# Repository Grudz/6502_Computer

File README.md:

# 6502_Computer
This repository stores everything for my 6502 project. This includes schematics, datasheets, C scripts, and assembly programs
.
[Ben Eater](https://www.youtube.com/playlist?list=PLowKtXNTBypFbtuVMUVXNR0z1mu7dp7eH) designed a custom clock module and 6502 computer on a breadboard. I expanded on that project, by combining those and turning them into a PCB.

-----
### Pretty dope red PCB I designed (4 layers:wink:)

### My Breadboard, not too shabby:sunglasses:

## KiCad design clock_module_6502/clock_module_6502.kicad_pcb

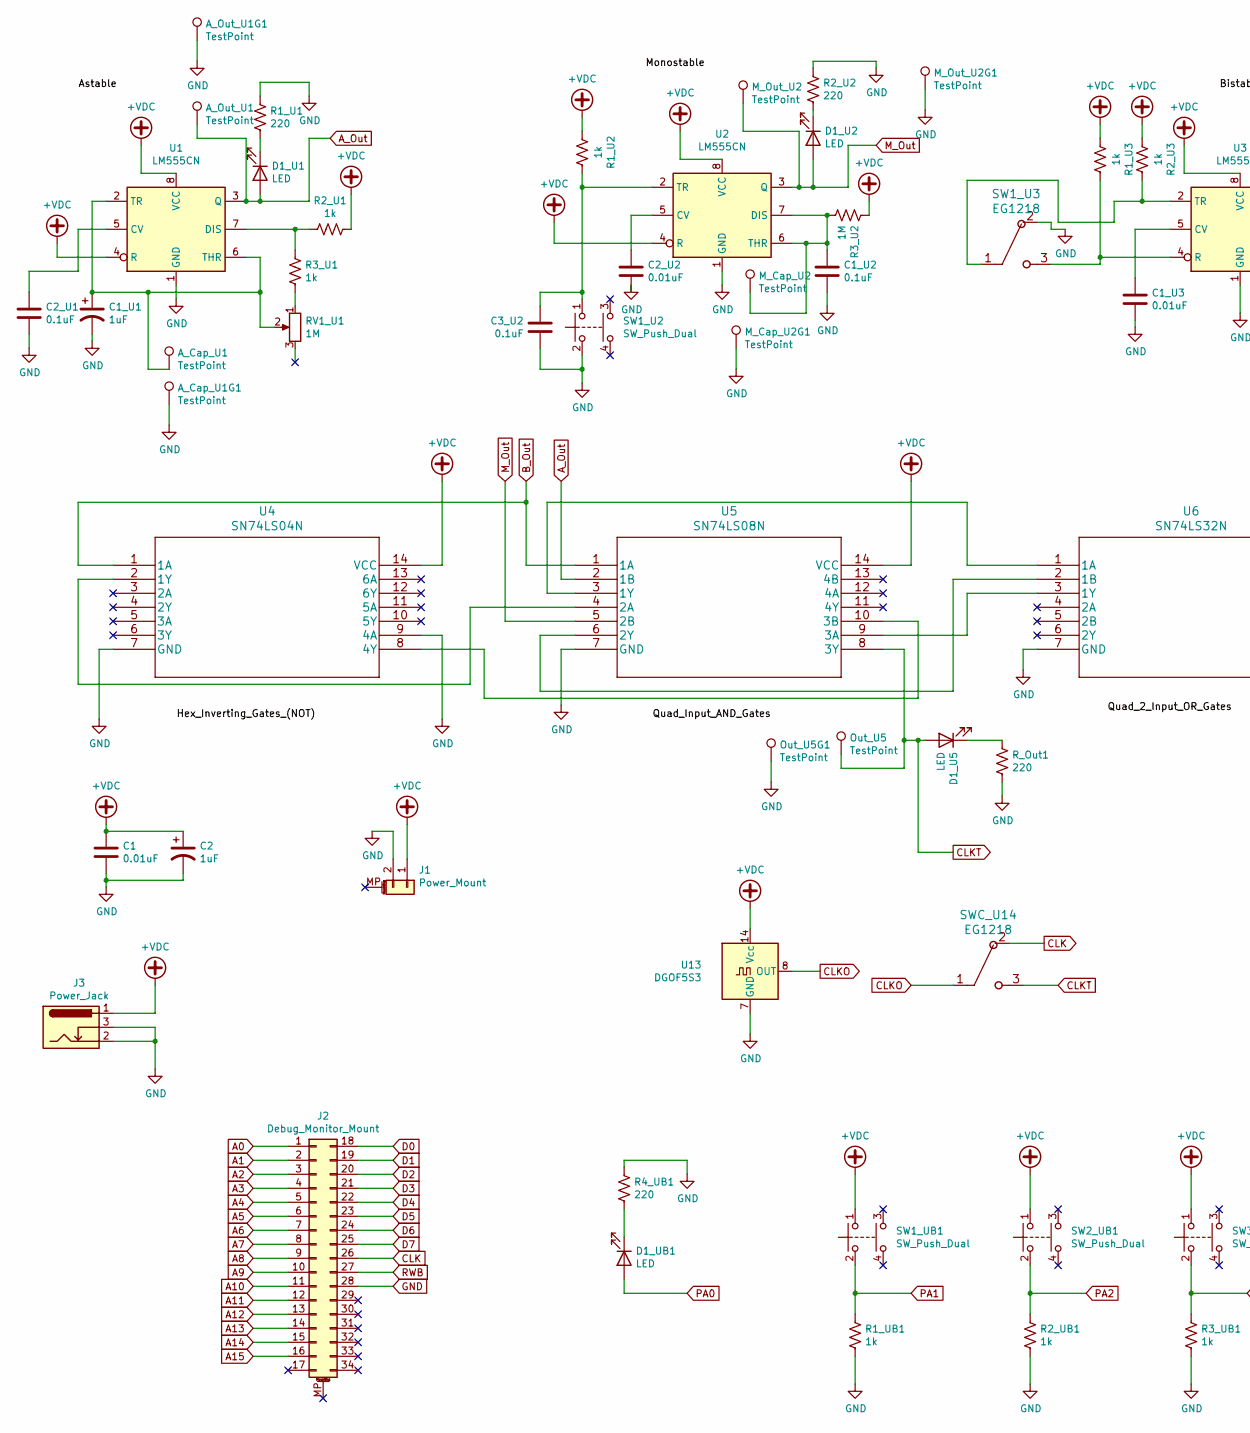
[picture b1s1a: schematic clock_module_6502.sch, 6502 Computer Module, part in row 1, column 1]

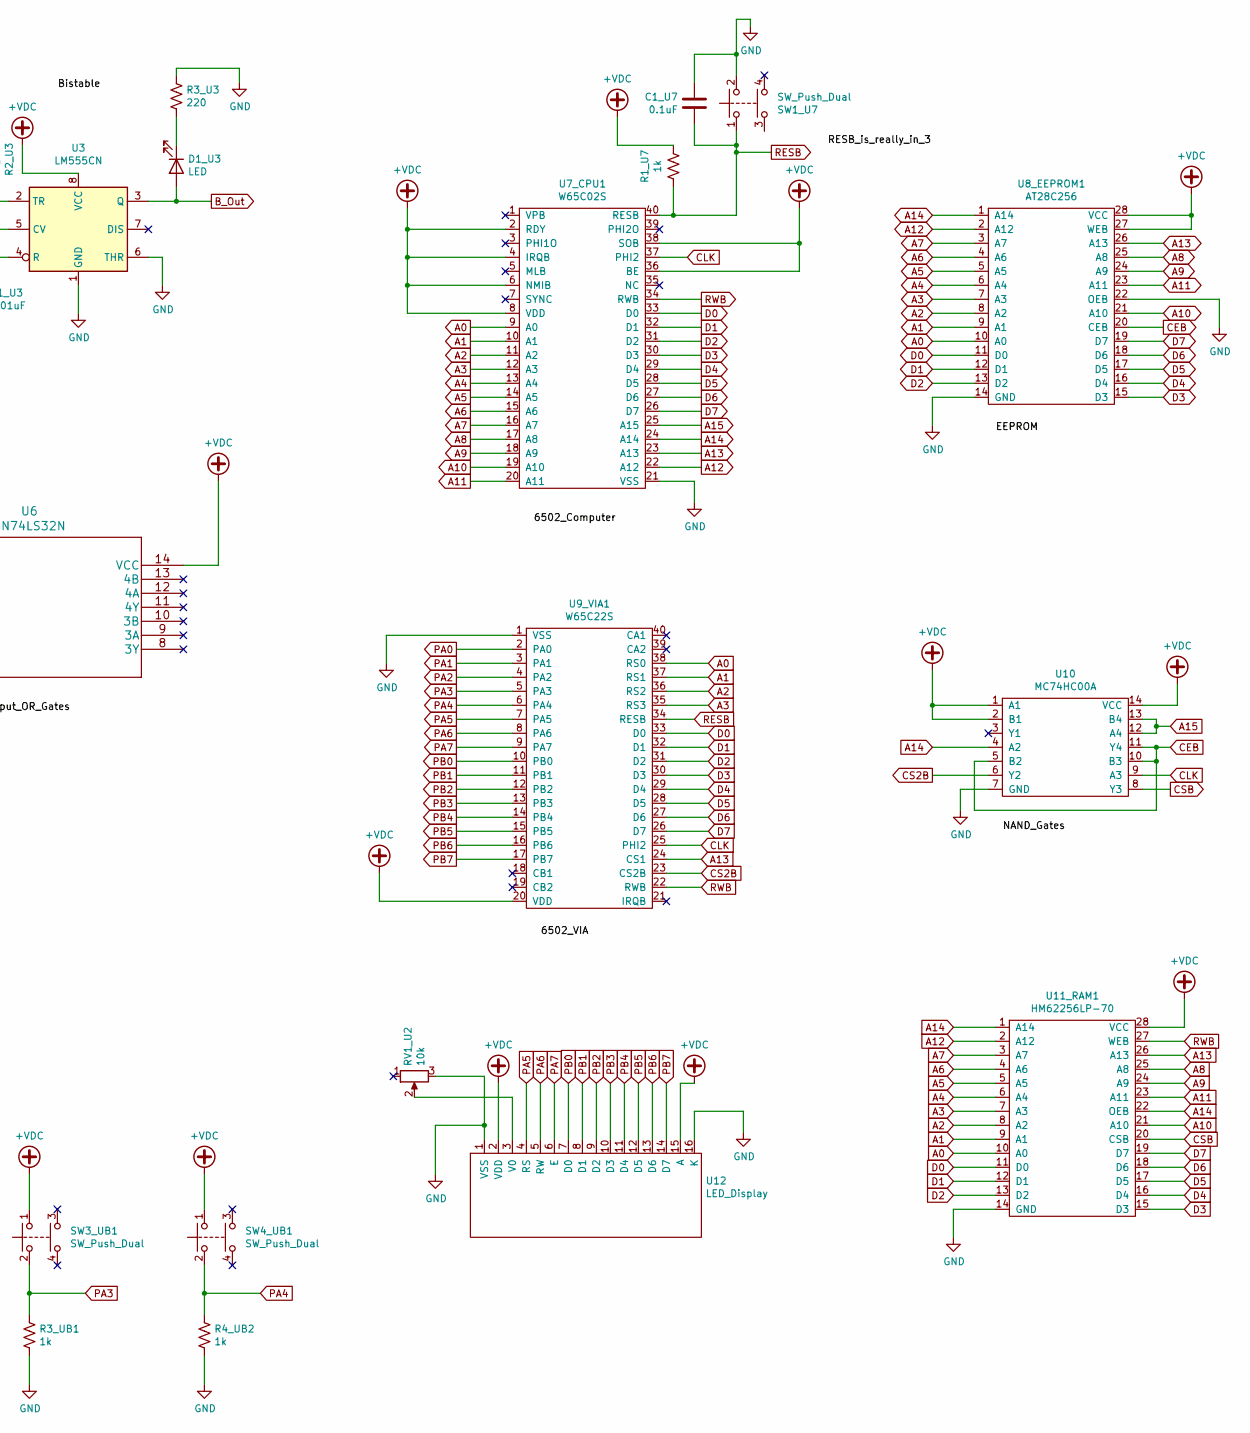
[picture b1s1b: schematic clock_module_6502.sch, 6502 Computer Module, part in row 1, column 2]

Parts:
A_Cap_U1, A_Cap_U1G1: TestPoint; TestPoint_Keystone_5000-5004_Miniature
A_Out_U1, A_Out_U1G1: TestPoint; TestPoint_Keystone_5000-5004_Miniature
C1, C1_U3, C2_U2: 0.01uF; C_Disc_D7.5mm_W5.0mm_P5.00mm
C1_U1, C2: 1uF; CP_Radial_D5.0mm_P2.50mm
C1_U2, C1_U7, C2_U1, C3_U2: 0.1uF; C_Disc_D7.5mm_W5.0mm_P5.00mm
D1_U1, D1_U2, D1_U3, D1_U5, D1_UB1: LED; LED_D3.0mm_FlatTop
J1: Power_Mount; PinHeader_1x02_P2.54mm_Vertical
J2: Debug_Monitor_Mount; PinHeader_2x17_P2.54mm_Vertical
J3: Power_Jack; BarrelJack_Horizontal
M_Cap_U2, M_Cap_U2G1: TestPoint; TestPoint_Keystone_5000-5004_Miniature
M_Out_U2, M_Out_U2G1: TestPoint; TestPoint_Keystone_5000-5004_Miniature
Out_U5, Out_U5G1: TestPoint; TestPoint_Keystone_5000-5004_Miniature
R1_U1, R2_U2, R3_U3, R4_UB1: 220; R_1206_3216Metric_Pad1.42x1.75mm_HandSolder
R1_U2, R1_U3, R1_U7, R1_UB1, R2_U1, R2_U3, R2_UB1, R3_U1, R3_UB1, R4_UB2: 1k; R_1206_3216Metric_Pad1.42x1.75mm_HandSolder
R3_U2: 1M; R_1206_3216Metric_Pad1.42x1.75mm_HandSolder
RV1_U1: 1M; Potentiometer_Bourns_3296W_Vertical
RV1_U2: 10k; Potentiometer_Bourns_3296W_Vertical
R_Out1: 220; R_1206_3216Metric_Pad1.42x1.75mm_HandSolder
SW1_U2, SW1_U7, SW1_UB1, SW2_UB1, SW3_UB1, SW4_UB1: SW_Push_Dual; SW_Tactile_Straight_KSL0Axx1LFTR
SW1_U3: EG1218
SWC_U14: EG1218
U1, U2, U3: LM555CN; DIP-8_W7.62mm
U4: SN74LS04N; SN74LS32N
U5: SN74LS08N; SN74LS32N
U6: SN74LS32N
U7_CPU1: W65C02S; DIP-40_W15.24mm_Socket
U8_EEPROM1: AT28C256; DIP-28_W15.24mm_Socket
U9_VIA1: W65C22S; DIP-40_W15.24mm_Socket
U10: MC74HC00A; SN74LS32N
U11_RAM1: HM62256LP-70; DIP-28_W15.24mm_Socket
U12: LED_Display; WC1602A
U13: DGOF5S3; Oscillator_DIP-14

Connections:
+VDC: C1.1, C2.1, J1.1, J3.1, R1_U2.2, R1_U3.2, R1_U7.1, R2_U1.1, R2_U3.2, R3_U2.2, SW1_UB1.1, SW2_UB1.1, SW3_UB1.1, SW4_UB1.1, U1.4 (R), U1.8 (VCC), U2.4 (R), U2.8 (VCC), U3.8 (VCC), U4.14 (VCC), U5.14 (VCC), U6.14 (VCC), U7_CPU1.2 (RDY), U7_CPU1.4 (IRQB), U7_CPU1.6 (NMIB), U7_CPU1.8 (VDD), U7_CPU1.36 (BE), U7_CPU1.38 (SOB), U8_EEPROM1.27 (WEB), U8_EEPROM1.28 (VCC), U9_VIA1.20 (VDD), U10.1 (A1), U10.2 (B1), U10.14 (VCC), U11_RAM1.28 (VCC), U12.2 (VDD), U12.15 (A), U13.14 (Vcc)
A0: J2.1, U7_CPU1.9 (A0), U8_EEPROM1.10 (A0), U9_VIA1.38 (RS0), U11_RAM1.10 (A0)
A1: J2.2, U7_CPU1.10 (A1), U8_EEPROM1.9 (A1), U9_VIA1.37 (RS1), U11_RAM1.9 (A1)
A2: J2.3, U7_CPU1.11 (A2), U8_EEPROM1.8 (A2), U9_VIA1.36 (RS2), U11_RAM1.8 (A2)
A3: J2.4, U7_CPU1.12 (A3), U8_EEPROM1.7 (A3), U9_VIA1.35 (RS3), U11_RAM1.7 (A3)
A4: J2.5, U7_CPU1.13 (A4), U8_EEPROM1.6 (A4), U11_RAM1.6 (A4)
A5: J2.6, U7_CPU1.14 (A5), U8_EEPROM1.5 (A5), U11_RAM1.5 (A5)
A6: J2.7, U7_CPU1.15 (A6), U8_EEPROM1.4 (A6), U11_RAM1.4 (A6)
A7: J2.8, U7_CPU1.16 (A7), U8_EEPROM1.3 (A7), U11_RAM1.3 (A7)
A8: J2.9, U7_CPU1.17 (A8), U8_EEPROM1.25 (A8), U11_RAM1.25 (A8)
A9: J2.10, U7_CPU1.18 (A9), U8_EEPROM1.24 (A9), U11_RAM1.24 (A9)
A10: J2.11, U7_CPU1.19 (A10), U8_EEPROM1.21 (A10), U11_RAM1.21 (A10)
A11: J2.12, U7_CPU1.20 (A11), U8_EEPROM1.23 (A11), U11_RAM1.23 (A11)
A12: J2.13, U7_CPU1.22 (A12), U8_EEPROM1.2 (A12), U11_RAM1.2 (A12)
A13: J2.14, U7_CPU1.23 (A13), U8_EEPROM1.26 (A13), U9_VIA1.24 (CS1), U11_RAM1.26 (A13)
A14: J2.15, U7_CPU1.24 (A14), U8_EEPROM1.1 (A14), U10.4 (A2), U11_RAM1.1 (A14), U11_RAM1.22 (OEB)
A15: J2.16, U7_CPU1.25 (A15), U10.12 (A4), U10.13 (B4)
A_Out: A_Out_U1.1, D1_U1.2 (A), U1.3 (Q), U5.2 (1B)
B_Out: D1_U3.2 (A), U3.3 (Q), U4.1 (1A), U5.1 (1A)
CEB: U8_EEPROM1.20 (CEB), U10.5 (B2), U10.10 (B3), U10.11 (Y4)
CLK: J2.26, SWC_U14.2, U7_CPU1.37 (PHI2), U9_VIA1.25 (PHI2), U10.9 (A3)
CLKO: SWC_U14.1, U13.8 (OUT)
CLKT: D1_U5.2 (A), Out_U5.1, SWC_U14.3, U5.8 (3Y)
CS2B: U9_VIA1.23 (CS2B), U10.6 (Y2)
CSB: U10.8 (Y3), U11_RAM1.20 (CSB)
D0: J2.18, U7_CPU1.33 (D0), U8_EEPROM1.11 (D0), U9_VIA1.33 (D0), U11_RAM1.11 (D0)
D1: J2.19, U7_CPU1.32 (D1), U8_EEPROM1.12 (D1), U9_VIA1.32 (D1), U11_RAM1.12 (D1)
D2: J2.20, U7_CPU1.31 (D2), U8_EEPROM1.13 (D2), U9_VIA1.31 (D2), U11_RAM1.13 (D2)
D3: J2.21, U7_CPU1.30 (D3), U8_EEPROM1.15 (D3), U9_VIA1.30 (D3), U11_RAM1.15 (D3)
D4: J2.22, U7_CPU1.29 (D4), U8_EEPROM1.16 (D4), U9_VIA1.29 (D4), U11_RAM1.16 (D4)
D5: J2.23, U7_CPU1.28 (D5), U8_EEPROM1.17 (D5), U9_VIA1.28 (D5), U11_RAM1.17 (D5)
D6: J2.24, U7_CPU1.27 (D6), U8_EEPROM1.18 (D6), U9_VIA1.27 (D6), U11_RAM1.18 (D6)
D7: J2.25, U7_CPU1.26 (D7), U8_EEPROM1.19 (D7), U9_VIA1.26 (D7), U11_RAM1.19 (D7)
GND: A_Cap_U1G1.1, A_Out_U1G1.1, C1.2, C1_U1.2, C1_U2.2, C1_U3.2, C1_U7.1, C2.2, C2_U1.2, C2_U2.2, C3_U2.2, J1.2, J2.28, J3.2, J3.3, M_Cap_U2G1.1, M_Out_U2G1.1, Out_U5G1.1, R1_U1.2, R1_UB1.1, R2_U2.2, R2_UB1.1, R3_U3.2, R3_UB1.1, R4_UB1.2, R4_UB2.1, RV1_U2.3, R_Out1.1, SW1_U2.2, SW1_U3.2, SW1_U7.2, U1.1 (GND), U2.1 (GND), U3.1 (GND), U3.6 (THR), U4.7 (GND), U4.9 (4A), U5.7 (GND), U6.7 (GND), U7_CPU1.21 (VSS), U8_EEPROM1.14 (GND), U8_EEPROM1.22 (OEB), U9_VIA1.1 (VSS), U10.7 (GND), U11_RAM1.14 (GND), U12.1 (VSS), U12.16 (K), U13.7 (GND)
M_Out: D1_U2.2 (A), M_Out_U2.1, U2.3 (Q), U5.5 (2B)
unnamed: A_Cap_U1.1, C1_U1.1, RV1_U1.2, U1.2 (TR), U1.6 (THR)
unnamed: C1_U2.1, M_Cap_U2.1, R3_U2.1, U2.6 (THR), U2.7 (DIS)
unnamed: C1_U3.1, U3.5 (CV)
unnamed: C2_U1.1, U1.5 (CV)
unnamed: C2_U2.1, U2.5 (CV)
unnamed: C3_U2.1, R1_U2.1, SW1_U2.1, U2.2 (TR)
unnamed: D1_U1.1 (K), R1_U1.1
unnamed: D1_U2.1 (K), R2_U2.1
unnamed: D1_U3.1 (K), R3_U3.1
unnamed: D1_U5.1 (K), R_Out1.2
unnamed: D1_UB1.1 (K), R4_UB1.1
unnamed: R1_U3.1, SW1_U3.3, U3.4 (R)
unnamed: R2_U1.2, R3_U1.2, U1.7 (DIS)
unnamed: R2_U3.1, SW1_U3.1, U3.2 (TR)
unnamed: R3_U1.1, RV1_U1.1
unnamed: RV1_U2.2, U12.3 (V0)
unnamed: U4.2 (1Y), U5.4 (2A)
unnamed: U4.8 (4Y), U5.10 (3B)
unnamed: U5.3 (1Y), U6.1 (1A)
unnamed: U5.6 (2Y), U6.2 (1B)
unnamed: U5.9 (3A), U6.3 (1Y)
PA0: D1_UB1.2 (A), U9_VIA1.2 (PA0)
PA1: R1_UB1.2, SW1_UB1.2, U9_VIA1.3 (PA1)
PA2: R2_UB1.2, SW2_UB1.2, U9_VIA1.4 (PA2)
PA3: R3_UB1.2, SW3_UB1.2, U9_VIA1.5 (PA3)
PA4: R4_UB2.2, SW4_UB1.2, U9_VIA1.6 (PA4)
PA5: U9_VIA1.7 (PA5), U12.4 (RS)
PA6: U9_VIA1.8 (PA6), U12.5 (RW)
PA7: U9_VIA1.9 (PA7), U12.6 (E)
PB0: U9_VIA1.10 (PB0), U12.7 (D0)
PB1: U9_VIA1.11 (PB1), U12.8 (D1)
PB2: U9_VIA1.12 (PB2), U12.9 (D2)
PB3: U9_VIA1.13 (PB3), U12.10 (D3)
PB4: U9_VIA1.14 (PB4), U12.11 (D4)
PB5: U9_VIA1.15 (PB5), U12.12 (D5)
PB6: U9_VIA1.16 (PB6), U12.13 (D6)
PB7: U9_VIA1.17 (PB7), U12.14 (D7)
RESB: C1_U7.2, R1_U7.2, SW1_U7.1, U7_CPU1.40 (RESB), U9_VIA1.34 (RESB)
RWB: J2.27, U7_CPU1.34 (RWB), U9_VIA1.22 (RWB), U11_RAM1.27 (WEB)

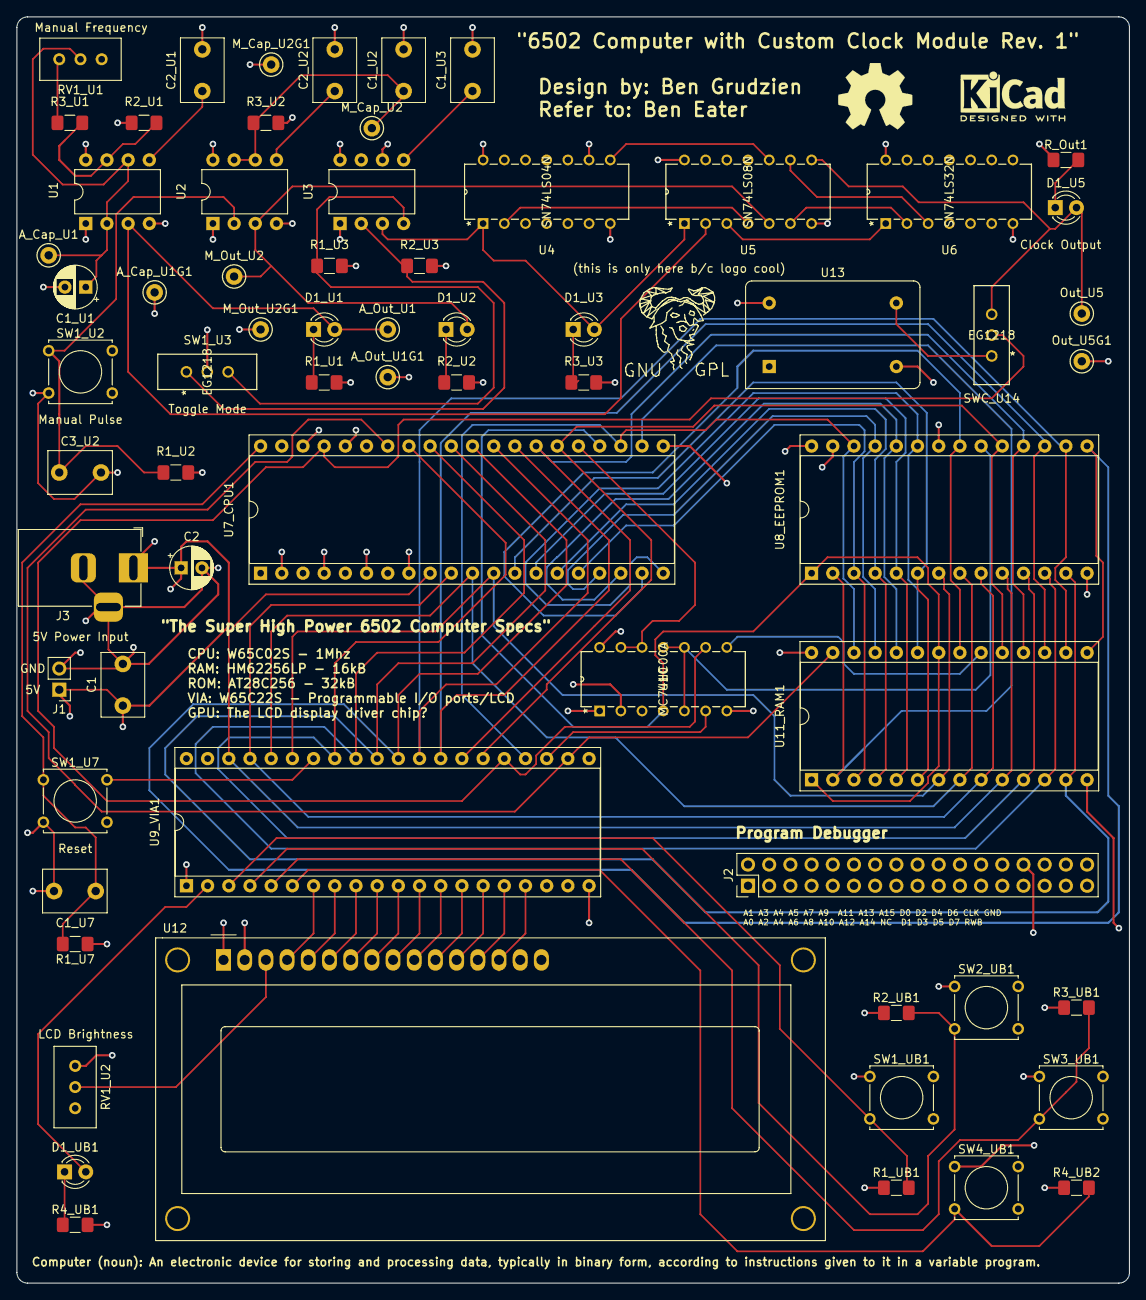
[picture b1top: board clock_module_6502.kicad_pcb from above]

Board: 4 copper layers, 133.3 x 151.8 mm, 67 parts (0 on the bottom side), 74 nets.

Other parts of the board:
(this is only here b/c logo cool): Symbol_GNU-Logo_SilkscreenTop

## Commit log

2020-08-07 Rename computer_6502.ino to computer_6502_Debug.ino

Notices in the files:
parts and their libraries:
Copyright 2016 Accelerated Designs. All rights reserved.
